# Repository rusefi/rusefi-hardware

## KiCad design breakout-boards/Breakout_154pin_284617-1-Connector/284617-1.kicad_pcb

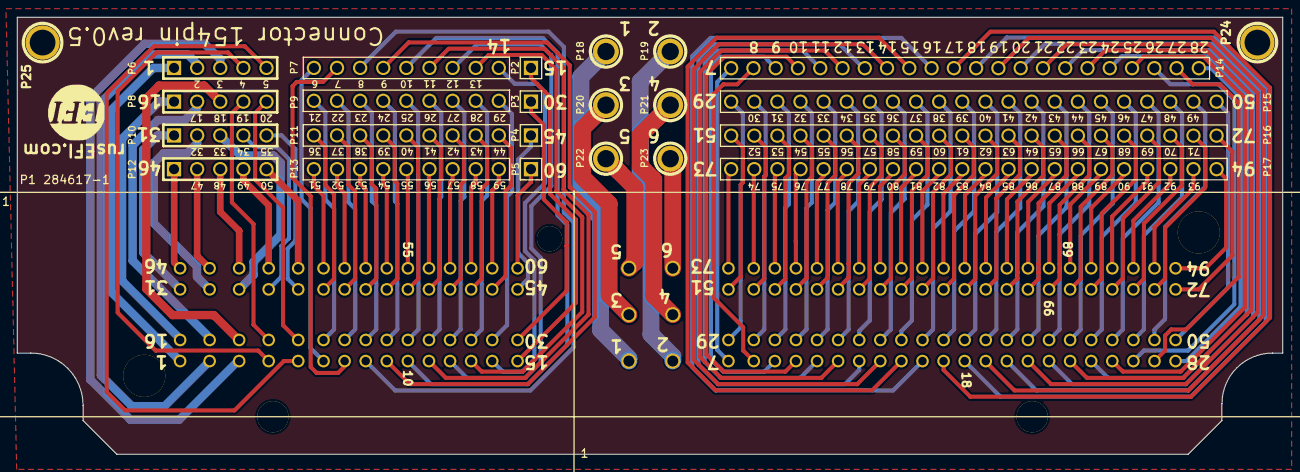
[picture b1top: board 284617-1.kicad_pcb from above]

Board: 2 copper layers, 150.0 x 51.8 mm, 27 parts (1 on the bottom side), 155 nets.

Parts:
G?: LOGO
G?#2: LOGO; LOGO_F
P1: 284617-1
P2, P3, P4, P5: CONN_1; PIN_ARRAY_1
P6, P8, P10, P12: CONN_5; PIN_ARRAY_5x1
P7, P9, P11, P13: CONN_9; PIN_ARRAY_9x1
P14, P15, P16, P17: CONN_22; PIN_ARRAY_22x1
P18, P19, P20, P21, P22, P23: CONN_1; 1pin(m)
P24, P25: CONN_1; 1pin

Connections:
/GND: P24.1, P25.1
unnamed: P1.94, P15.6
unnamed: P1.108, P15.20
unnamed: P1.107, P15.19
unnamed: P1.106, P15.18
unnamed: P1.105, P15.17
unnamed: P1.104, P15.16
unnamed: P1.103, P15.15
unnamed: P1.102, P15.14
unnamed: P1.101, P15.13
unnamed: P1.100, P15.12
unnamed: P1.99, P15.11
unnamed: P1.98, P15.10
unnamed: P1.97, P15.9
unnamed: P1.96, P15.8
unnamed: P1.95, P15.7
unnamed: P1.109, P15.21
unnamed: P1.93, P15.5
unnamed: P1.92, P15.4
unnamed: P1.91, P15.3
unnamed: P1.90, P15.2
unnamed: P1.89, P15.1
unnamed: P1.88, P14.22
unnamed: P1.87, P14.21
unnamed: P1.86, P14.20
unnamed: P1.85, P14.19
unnamed: P1.84, P14.18
unnamed: P1.83, P14.17
unnamed: P1.82, P14.16
unnamed: P1.81, P14.15
unnamed: P1.80, P14.14
unnamed: P1.123, P16.13
unnamed: P1.137, P17.5
unnamed: P1.136, P17.4
unnamed: P1.135, P17.3
unnamed: P1.134, P17.2
unnamed: P1.133, P17.1
unnamed: P1.132, P16.22
unnamed: P1.131, P16.21
unnamed: P1.130, P16.20
unnamed: P1.129, P16.19
unnamed: P1.128, P16.18
unnamed: P1.127, P16.17
unnamed: P1.126, P16.16
unnamed: P1.125, P16.15
unnamed: P1.124, P16.14
unnamed: P1.79, P14.13
unnamed: P1.122, P16.12
unnamed: P1.121, P16.11
unnamed: P1.120, P16.10
unnamed: P1.119, P16.9
unnamed: P1.118, P16.8
unnamed: P1.117, P16.7
unnamed: P1.116, P16.6
unnamed: P1.115, P16.5
unnamed: P1.114, P16.4
unnamed: P1.113, P16.3
unnamed: P1.112, P16.2
unnamed: P1.111, P16.1
unnamed: P1.110, P15.22
unnamed: P1.138, P17.6
unnamed: P1.78, P14.12
unnamed: P1.77, P14.11
unnamed: P1.76, P14.10
unnamed: P1.75, P14.9
unnamed: P1.74, P14.8
unnamed: P1.73, P14.7
unnamed: P1.72, P14.6
unnamed: P1.71, P14.5
unnamed: P1.70, P14.4
unnamed: P1.69, P14.3
unnamed: P1.68, P14.2
unnamed: P1.67, P14.1
unnamed: P1.154, P17.22
unnamed: P1.144, P17.12
unnamed: P1.153, P17.21
unnamed: P1.143, P17.11
unnamed: P1.152, P17.20
unnamed: P1.142, P17.10
unnamed: P1.151, P17.19
unnamed: P1.141, P17.9
unnamed: P1.150, P17.18
unnamed: P1.140, P17.8
unnamed: P1.147, P17.15
unnamed: P1.149, P17.17
unnamed: P1.139, P17.7
unnamed: P1.148, P17.16
unnamed: P1.146, P17.14
unnamed: P1.145, P17.13
unnamed: P1.62, P19.1
unnamed: P1.61, P18.1
unnamed: P1.45, P4.1
unnamed: P1.63, P20.1
unnamed: P1.66, P23.1
unnamed: P1.65, P22.1
unnamed: P1.64, P21.1
unnamed: P1.1, P6.1
unnamed: P1.59, P13.9
unnamed: P1.49, P12.4
unnamed: P1.60, P5.1
unnamed: P1.43, P11.8
unnamed: P1.33, P10.3
unnamed: P1.23, P9.3
unnamed: P1.13, P7.8
unnamed: P1.52, P13.2
unnamed: P1.42, P11.7
unnamed: P1.32, P10.2
unnamed: P1.22, P9.2
unnamed: P1.12, P7.7
unnamed: P1.51, P13.1
unnamed: P1.41, P11.6
unnamed: P1.31, P10.1
unnamed: P1.21, P9.1
unnamed: P1.11, P7.6
unnamed: P1.53, P13.3
unnamed: P1.50, P12.5
unnamed: P1.40, P11.5
unnamed: P1.30, P3.1
unnamed: P1.20, P8.5
unnamed: P1.10, P7.5
unnamed: P1.9, P7.4
unnamed: P1.8, P7.3
unnamed: P1.7, P7.2
unnamed: P1.6, P7.1
unnamed: P1.5, P6.5
unnamed: P1.4, P6.4
unnamed: P1.3, P6.3
unnamed: P1.2, P6.2
unnamed: P1.46, P12.1
unnamed: P1.39, P11.4
unnamed: P1.29, P9.9
unnamed: P1.19, P8.4
unnamed: P1.48, P12.3
unnamed: P1.38, P11.3
unnamed: P1.28, P9.8
unnamed: P1.18, P8.3
unnamed: P1.57, P13.7
unnamed: P1.47, P12.2
unnamed: P1.37, P11.2
unnamed: P1.27, P9.7
unnamed: P1.17, P8.2
unnamed: P1.56, P13.6
unnamed: P1.58, P13.8
unnamed: P1.36, P11.1
unnamed: P1.26, P9.6
unnamed: P1.16, P8.1
unnamed: P1.55, P13.5
unnamed: P1.35, P10.5
unnamed: P1.25, P9.5
unnamed: P1.15, P2.1
unnamed: P1.54, P13.4
unnamed: P1.44, P11.9
unnamed: P1.34, P10.4
unnamed: P1.24, P9.4
unnamed: P1.14, P7.9

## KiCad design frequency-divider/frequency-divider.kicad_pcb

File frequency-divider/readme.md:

We sometimes want to lower input frequency unless one does hard code periperal based magic.

https://github.com/rusefi/rusefi/issues/2935

https://github.com/rusefi/rusefi/issues/3412

https://github.com/rusefi/rusefi/issues/7133

See also https://github.com/rusefi/rusefi-hardware/tree/main/VR_ncv1124_test_module

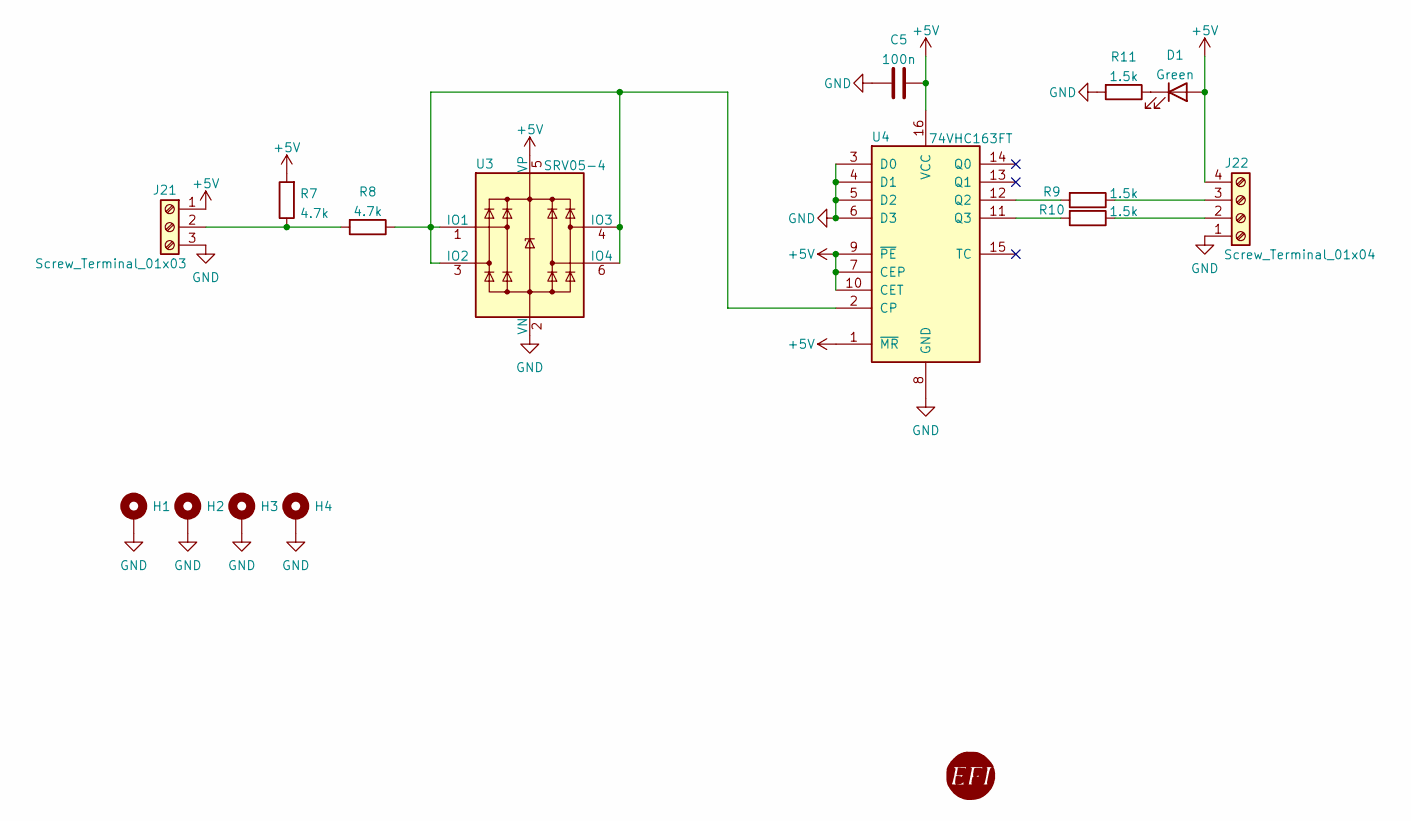
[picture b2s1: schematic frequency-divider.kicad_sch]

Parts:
C5: 100n; C_0603_1608Metric_Pad1.08x0.95mm_HandSolder; LCSC C14663
D1: Green; LED_0805_2012Metric_Pad1.15x1.40mm_HandSolder; LCSC C2297
G8: RUSEFI_LOGO; rusefi_logo
H1, H2, H3, H4: MountingHole_Pad; MountingHole_3.2mm_M3_Pad_Via
J21: Screw_Terminal_01x03; TerminalBlock_MetzConnect_Type055_RT01503HDWU_1x03_P5.00mm_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; LCSC C128026
J22: Screw_Terminal_01x04; TerminalBlock_MetzConnect_Type055_RT01504HDWU_1x04_P5.00mm_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; LCSC C173286
R7, R8: 4.7k; R_0603_1608Metric_Pad0.98x0.95mm_HandSolder; LCSC C23162
R9, R10, R11: 1.5k; R_0603_1608Metric_Pad0.98x0.95mm_HandSolder; LCSC C22843
U3: SRV05-4; SOT-23-6; LCSC C85364
U4: 74VHC163FT; TSSOP-16_4.4x5mm_P0.65mm; LCSC C150161

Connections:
+5V: C5.2, D1.2 (A), J21.1, J22.4, R7.2, U3.5 (VP), U4.1 (~MR), U4.7 (CEP), U4.9 (~PE), U4.10 (CET), U4.16 (VCC)
GND: C5.1, H1.1, H2.1, H3.1, H4.1, J21.3, J22.1, R11.2, U3.2 (VN), U4.3 (D0), U4.4 (D1), U4.5 (D2), U4.6 (D3), U4.8 (GND)
unnamed: D1.1 (K), R11.1
unnamed: J21.2, R7.1, R8.2
unnamed: J22.2, R10.1
unnamed: J22.3, R9.1
unnamed: R8.1, U3.1 (IO1), U3.3 (IO2), U3.4 (IO3), U3.6 (IO4), U4.2 (CP)
unnamed: R9.2, U4.12 (Q2)
unnamed: R10.2, U4.11 (Q3)

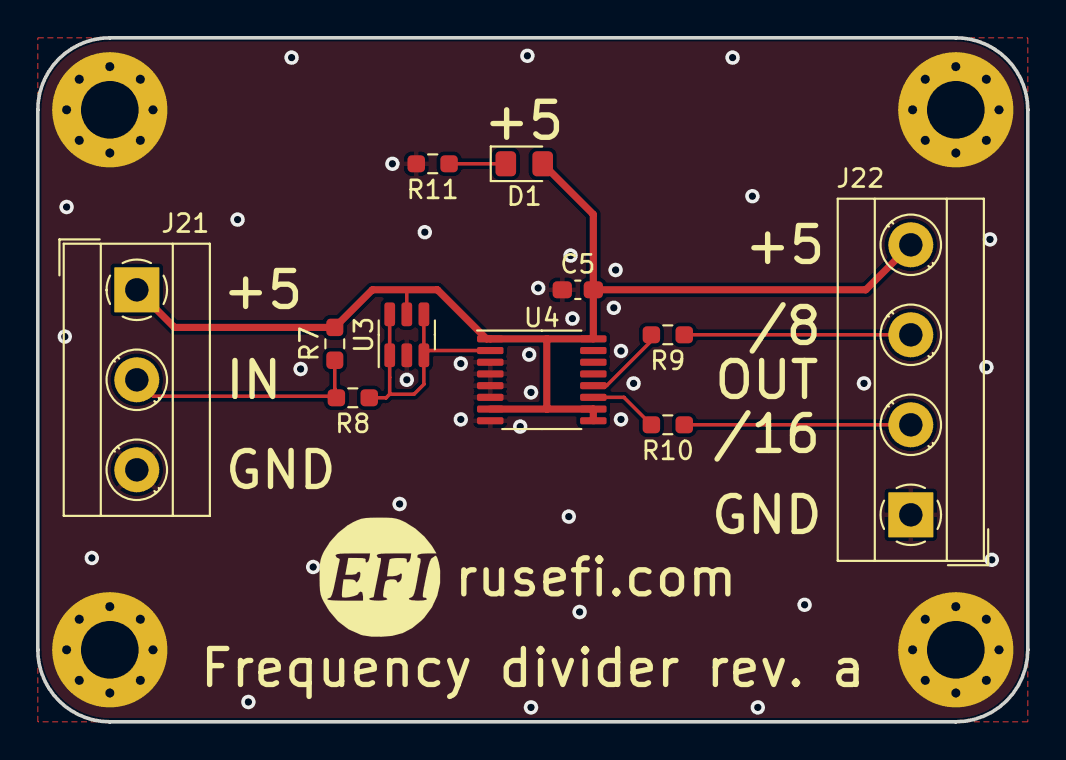
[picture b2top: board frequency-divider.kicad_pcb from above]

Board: 2 copper layers, 55.0 x 38.0 mm, 16 parts (0 on the bottom side), 9 nets.

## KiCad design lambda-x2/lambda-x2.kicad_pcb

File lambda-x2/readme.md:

# About

🟢 rev1 is known to work 🟢

pinout source https://github.com/rusefi/rusefi/tree/master/firmware/config/boards/lambda-x2

https://www.shop.rusefi.com/shop/p/dual-channel-wbo

Features:
* STM32F103 dual channel wideband AFR controller supporting Bosch LSU4.9 and LSU4.2 (LSU_ADV work in progress)
* CAN and analog output
* Bluetooth or USRT TunerStudio connectivity

Options (not icluded in default BOM)
* x2 EGT input using MAX31855KASA or MAX31856
* x2 auxilary analog input: 0..5V with pull-up or pull-down (configurable by soldering resistor). One can be used to source 5V to external sensor.
* x2 2 auxilary output 0..5V. Also can be used for slow PWM signal output.
* x2 open drain outputs

In development:
* MegaSquirt compatible pass-through connection over CAN http://www.msgpio.com/manuals/mshift/cpt.html (in progress)

See [interactive pinout](https://rusefi.com/docs/pinouts/lambda-x2/)

See [wire colors](https://github.com/rusefi/rusefi/wiki/WBO#naming-convention) for standart LSU wire collors and connectors pinouts.

Current stable [FW release](https://github.com/dron0gus/wideband/releases/tag/release_zero) use "dual-rev1" files

Firmware [sources](https://github.com/dron0gus/wideband) (based on https://github.com/mck1117/wideband).

See rusEFI forum: [F103 dual channel wideband controller + EGT + 2 x AUX In + 2 Aux out](https://rusefi.com/forum/viewtopic.php?f=4&t=2314)

See also https://github.com/rusefi/rusefi/wiki/WBO

# Known issues

## DFU mode/floating PB2

BOOT0 = 1, BOOT1 = 0 pattern is used to enter DFU bootloader on power/reset. BOOT0 is controled by jumper/button. BOOT1 (PB2) is used as bias current source for LSU4.9 and floating.

Use jumper wire to connect PB2 (through bias resistor) to GND: connect A2 pin of main connector with GND (J4 AUX connector pin 10)

## ESR measurement crosstalk between channels (rev0 and rev1)

HW has three different outputs for Nernst cell ESR measurement with different output resistance: 6.8K for LSU4.2, 22K for LSU4.9 and 47K for LSUADV. Idea was to allow the user to set the type of sensor from SW only.

Each ESR output is driven by one MCU GPIO. GPIOs for unused ESR measurement outputs are kept in Hi-Z (input) state and does not affect ESR measurement.

Same GPIO drivers ESR outputs for both channels. **This is the root cause of problem**

Problem: unused ESR output with GPIO in Hi-Z state connect Nernst cell outputs from left and right channel through two resistors. This causes crosstalk between channels and inaccurate ESR measurement. Wrong ESR measurement causes incorrect sensor temperature calculation. This can lead to inaccurate AFR measurement, overheating or underheating of the sensor.

Same issue for LSU4.9 bias resistors R22 and R70.

Solution:

Boards come with all ESR drive resistors populated. You have to remove unnecessary resistors.

If LSU4.2 sensor is used: remove R24, R25, R71, R72, R22, R70. Keep R41 and R73 - 6.8K

If LSU4.9 sensor is used: remove R25, R41, R72, R73. Keep R24 and R71 - 22K

If LSUADV sensor is used: remove R24, R41, R71, R73, R22, R70. Keep R25 and R72 - 47K

This will be (or not) solved in next revision of HW.

# Pinout

## Connectors pinout

[Main connector interactive Pinout](https://rusefi.com/docs/pinouts/lambda-x2/)

J4 is AUX connector available on PCB. SPI and I2C interfaces along with 3.3V and 5V are routed to this connector. Can be used to connect some small disply (SW not implemented yet)

J3 connector is for flashing and powering board on table. Also can be used for TunerStudion connection.

J1 and J2 are JTAG connectos.

## Uart pinout

J3 connector. Colors are default for cheap usb-to-uart converters based on CP2101 or FTDI232
Connect red wire if you want to power device from USB.
Default baud rate is 115200.

# Bluetooth

No extra steps needed to initialize JDY-33. Default device name is "RusEFI WBO x2" (or "RuseEFI WBO x2 BLE" for BT BLE)

Default baud rate is 115200.

# TunerStudio configuration

Baudrate is 115200
[.ini file](https://github.com/dron0gus/wideband/blob/master/firmware/ini/rusefi_wb_f1_dual.ini) for both UART and BT connection.

Both interfaces can be used simultaneously for data logging but not for settings change (from rev1).

Rev0 share same UART for both interfaces.

# Firmware Upload

Two ways to program using STM32CubeProgrammer

* recommended way: using UART connectivity. Power device up while shorting BOOT0 jumper to enter DFU mode (see "DFU mode/floating PB2" issue above)
* st-link if you have tc2030 spring-loaded cable.
* update over CAN or UART (J3) using OpenBLT (update over BT is in progress)

TL,DR: 9600 nothing connected on main connector

## Updating over UART using DFU mode

1. Disconnect main connector. If you are going to apply +12V power through main connector - make sure that nothing else is connected to WBO (LSU sensors, any load, etc). But I recommend flash using +5V from USB.
   
2. connect USB to uart connector to J3 connector: gnd, rx and tx.
Don't forget to cross Rx-`Tx (adapter's Tx goes to WBO's Rx, WBO's Tx goes to adapter's Rx).
If you going to power WBO from USB port - also attach 5V line. Do not connect +5 from USB adapter if you are going to use +12V supply through main connector.

### Linux way

3. Install stm32flash utility

`apt-get install stm32flash`

4. Press and hold BOOT0 button on the bottom of PCB. Or short BOOT0 PCB jumper if button is not populated on your board.

6. Run

`stm32flash /dev/ttyUSB0 -w wideband.hex`

### Windows way

3. Download and install STM32 Flash Loader Demonstrator. (Alternative tool is stm32flash - not covered in this instruction)

4. Figure out USB to serial serial port number: 

5. Start Flash Loader Demonstrator GUI application, select correct COM port. Optional: reduce timeout to 1 second:

6. Press and hold BOOT0 button on the bottom of PCB. Or short BOOT0 PCB jumper if button is not populated on your board.

7. Apply power (while holding BOOT0 button) to board and press Next in application. After app detects chip you should see something similar to:

8. Press next, select "Download to device", select wideband.bin file. Select "Jump to user application" and "Verify after download"

9. Press Next and wait for flash/verification ends.

## Updating using JTAG

DBD.

## Update using OpenBLT

OpenBLT https://www.feaser.com/openblt/doku.php

1. Restart device to OpenBLT mode using "Reset to OpenBLT" button under Controller -> ECU tools in TunerStudio.
   
2. Close TunerStudio to release serial port

3. Open BootCommander, select correct serial port, select wideband_update.srec file.

# Changelog

## rev 1
* Switch to 64 pin STM32/GD32
* Add 8MHz HSE oscillator (better clock stability for CAN over wide temperature range)
* Use DAC (instead of PWM) outputs for driving Ip
* Move BT to UART3/USART3, keep USART1 for bootloader/debug
* Drive BT's EN signal from MCU
* Fix RC filters on heater outputs for better voltage measurement
* Use separate ADC input for Vbat measurement
* Use ADC channels for AUX outputs monitoring/diagnostic
* Use PWM noise cancelation circuit on AUX analog outputs
* Removed useless/non-functional protection of Vm outputs
* Fix board outline to fit two types of enclosure ("plastic top" and "alloy brick")
* Add testpoints for TC2030 JTAG probe
* Add buttons for Reset and Boot0
* Add Cfg1 and jumpers
* Replace fuse holder with resettable 0.2A 33V fuse
* Two status LEDs for separate status indication for left and right channel
* Silkscreen labels around testpoints
* Silkscreen labels at uart connector on both sides of PCB
* Un_3x_sense formula is now 0.247 + 3.15 * (Un - Vm)
* Un_sense (not gained) is also routed to ADC input
* Protection from possible Ip current when MCU in reset/bootloader
* White "power on" LED replaced with green
* Main connector pinout added to top silkscreen
* AUX connector pinout added to top silkscreen

## rev 0

Seems to work with proper C10/C35 using https://github.com/rusefi/wideband/releases/tag/20230210-does-not-match-binaris

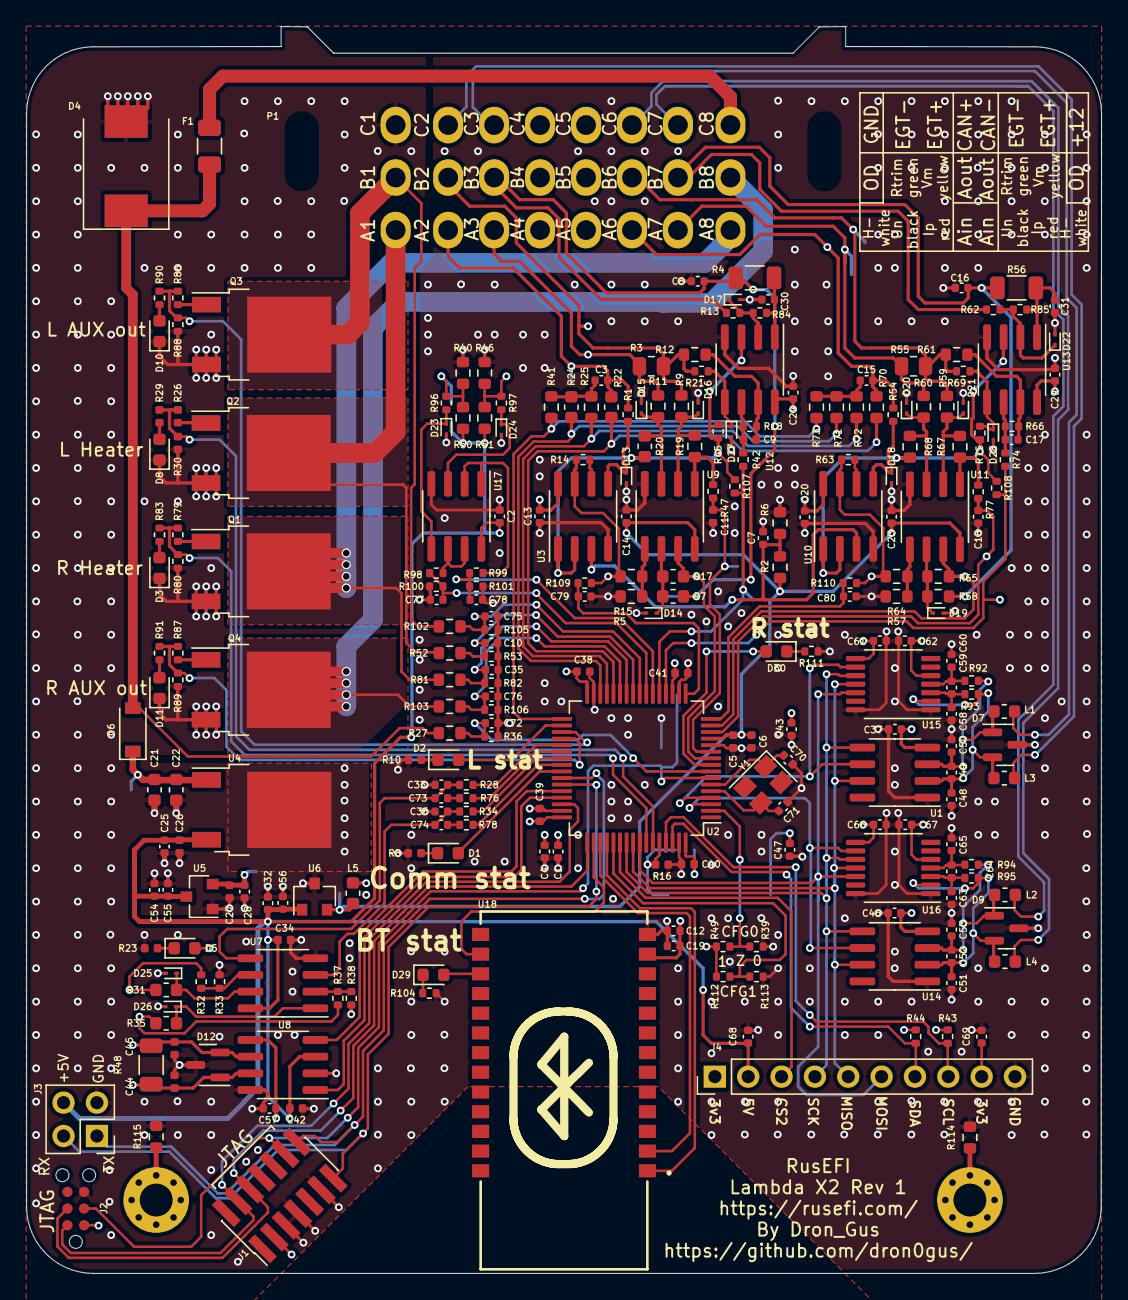
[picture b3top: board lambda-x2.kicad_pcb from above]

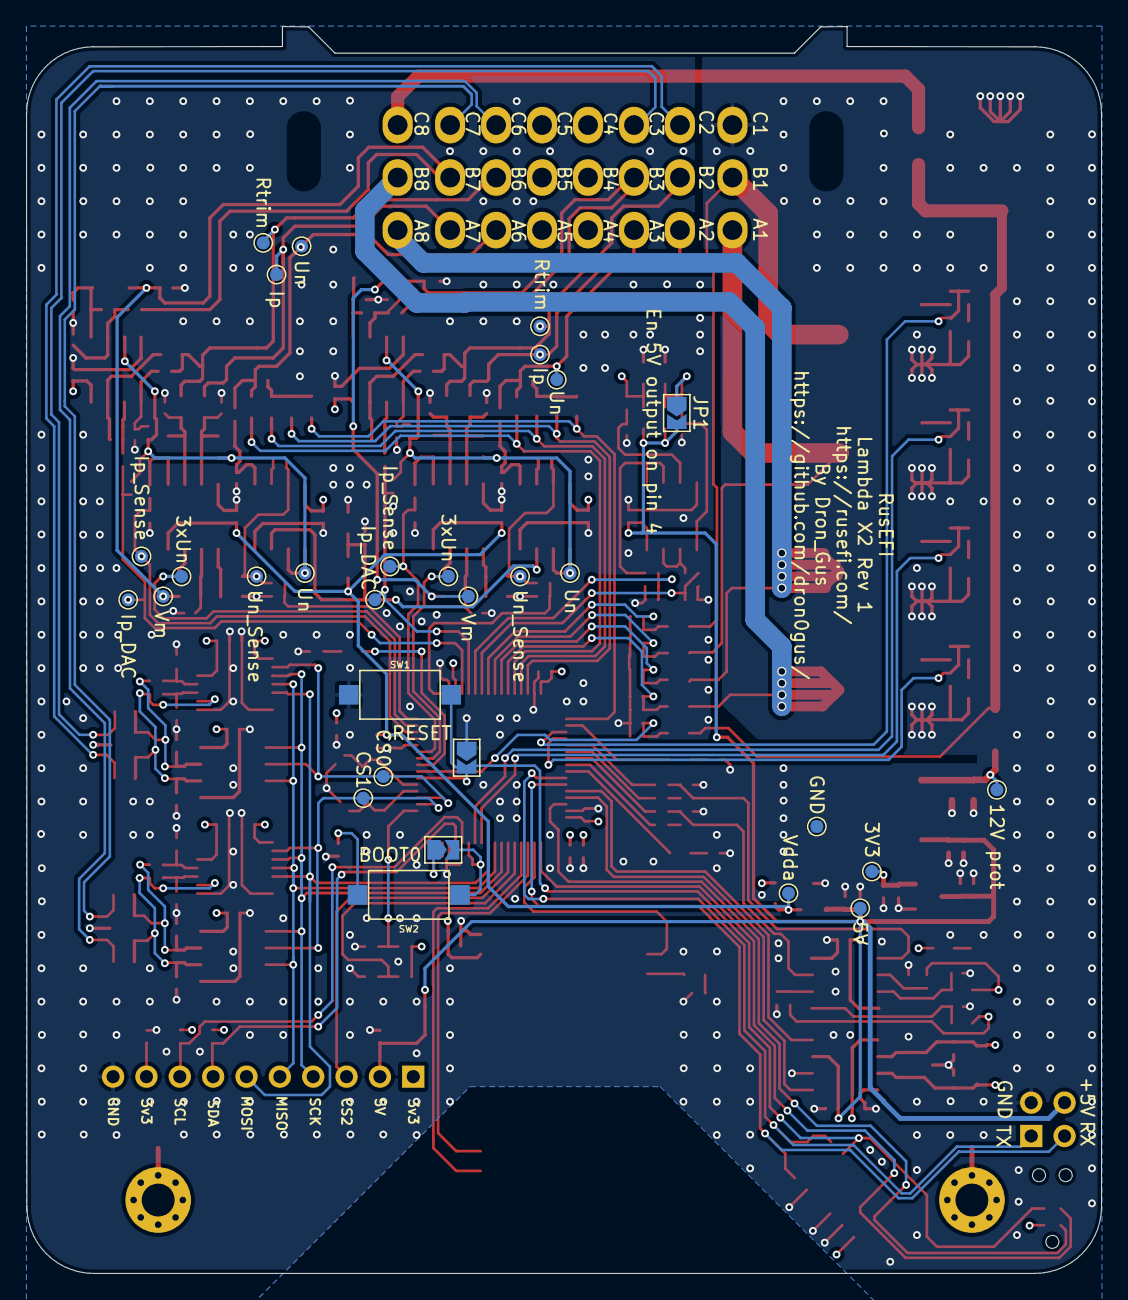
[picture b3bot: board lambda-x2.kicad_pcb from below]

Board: 4 copper layers, 81.9 x 95.0 mm, 291 parts (30 on the bottom side), 149 nets.

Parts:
C1, C6, C7, C8, C12, C16, C25, C28, C30, C31, C32, C43, C47, C54: 1u; C_0402_1005Metric
C2, C3, C5, C11, C13, C14, C15, C18, C19, C20, C23, C24, C26, C27, C29, C33, C34, C36, C37, C38, C39, C40, C41, C42, C46, C49, C52, C55, C56, C57, C59, C61, C62, C64, C66, C67, C68, C69, C73, C74: 100n; C_0402_1005Metric
C4: 4.7u; C_0402_1005Metric
C9, C17: 33n; C_0402_1005Metric
C10, C35, C72, C75, C76, C77, C78, C79, C80: 1n; C_0402_1005Metric
C21: 1u 25V; C_0603_1608Metric
C22: 100n 25V; C_0603_1608Metric
C44, C45: 47p; C_0402_1005Metric
C48, C50, C51, C53, C58, C60, C63, C65: 10nF 50V; C_0402_1005Metric
C70, C71: 20pF 50V; C_0402_1005Metric
D1: BLUE; LED_0603_1608Metric
D2, D5, D29, D30: GREEN; LED_0603_1608Metric
D3, D8, D10, D11: RED; LED_0603_1608Metric
D4: SMCJ22CA; D_SMC
D6: 1N4148W; D_SOD-123
D7, D9, D12: NUP2105L; SOT-23
D13, D14, D15, D16, D17, D18, D19, D20, D21, D22, D23, D24, D25, D26, D27, D28: ESD5V0D9B; D_SOD-923
F1: BSMD1206-025-33V; Fuse_1206_3216Metric
H1, H4: MountingHole_Pad; MountingHole_2.5mm_Pad_Via
J1: FTSH-107-01-F-DV-K; PinHeader_2x07_P1.27mm_Vertical_SMD
J2: tc2030-idc-nl
J3: Conn_02x02_Odd_Even; PinHeader_2x02_P2.54mm_Vertical
J4: Conn_01x10; PinHeader_1x10_P2.54mm_Vertical
JP1, JP2, JP3: SolderJumper_2_Open; SolderJumper-2_P1.3mm_Open_TrianglePad1.0x1.5mm
L1, L2, L3, L4, L5: 470R@100MHz; L_0603_1608Metric
P1: 33311-24AW-2
Q1, Q2, Q3, Q4: BTS3028; TO-252-2
R1, R14, R16, R18, R21, R30, R49, R54, R63, R66, R69, R80, R88, R89, R96, R97, R107, R108, R112: 10k; R_0402_1005Metric
R2, R5, R6, R7, R9, R11, R57, R58, R59, R60: 10k 0.1%; R_0603_1608Metric
R3, R55: 61.9R 1%; R_0805_2012Metric
R4, R56: 10R; R_1206_3216Metric
R8, R10, R23, R26, R29, R79, R83, R86, R87, R90, R91, R104, R109, R110, R111: 1k; R_0402_1005Metric
R12, R61, R114, R115: 47R; R_0603_1608Metric
R13, R36, R53, R62, R82, R84, R85, R105, R106: 10k 1%; R_0402_1005Metric
R15, R64: 2.7k 0.1%; R_0603_1608Metric
R17, R65: 30k 1%; R_0603_1608Metric
R19, R20, R67, R68: 100k 0.1%; R_0603_1608Metric
R22, R70: 62k 1%; R_0603_1608Metric
R24, R71: 22k 0.1%; R_0603_1608Metric
R25, R72: 47k 1%; R_0603_1608Metric
R27, R52, R81, R102, R103: 100k 1%; R_0603_1608Metric
R28, R34, R43, R44, R47, R76, R77, R78: 3.3k; R_0402_1005Metric
R31, R35: 330R; R_0603_1608Metric
R32, R37, R98, R99: 82k; R_0402_1005Metric
R33, R38, R100, R101: 160k; R_0402_1005Metric
R39, R113: 0R; R_0402_1005Metric
R40, R46, R50, R51: 1K; R_0603_1608Metric
R41, R73: 6.8k 0.1%; R_0603_1608Metric
R42, R45, R74, R75: 68k; R_0402_1005Metric
R48: 120R; R_1206_3216Metric
R92, R93, R94, R95: 100R; R_0402_1005Metric
SW1, SW2: SW_SPST_CK_RS282G05A3
TP3, TP4: Un_Sense; TestPoint_Pad_D1.0mm
TP5, TP6: 3xUn; TestPoint_Pad_D1.0mm
TP7: 5V; TestPoint_Pad_D1.0mm
TP8: 3V3; TestPoint_Pad_D1.0mm
TP9: Vdda; TestPoint_Pad_D1.0mm
TP10, TP17: Ip; TestPoint_Pad_D1.0mm
TP11, TP18: Rtrim; TestPoint_Pad_D1.0mm
TP12, TP19: Vm; TestPoint_Pad_D1.0mm
TP13, TP14, TP20, TP21: Un; TestPoint_Pad_D1.0mm
TP15, TP22: Ip_DAC; TestPoint_Pad_D1.0mm
TP16, TP23: Ip_Sense; TestPoint_Pad_D1.0mm
TP24: GND; TestPoint_Pad_D1.0mm
TP25: CS0; TestPoint_Pad_D1.0mm
TP26: CS1; TestPoint_Pad_D1.0mm
TP27: 12V prot; TestPoint_Pad_D1.0mm
U1, U14: MAX31855KASA; SOIC-8_3.9x4.9mm_P1.27mm
U2: STM32F103RCTx; LQFP-64_10x10mm_P0.5mm
U3, U7, U10, U12, U13, U17: MCP6002T-I/SN; SOIC-8_3.9x4.9mm_P1.27mm
U4: LM78M05_TO252; TO-252-2
U5: XC6206P332MR; SOT-23
U6: REF3033; SOT-23
U8: TJA1051T-3; SOIC-8_3.9x4.9mm_P1.27mm
U9, U11: GS8332-SR; SOIC-8_3.9x4.9mm_P1.27mm
U15, U16: MAX31856; TSSOP-14_4.4x5mm_P0.65mm
U18: JDY-33
Y1: XXDCELNANF-8MHZ; Crystal_SMD_3225-4Pin_3.2x2.5mm

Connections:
12V_RAW: F1.2, P1.24 (C8)
+3V3: C1.1, C4.1, C12.1, C13.1, C19.1, C20.1, C24.1, C27.1, C28.1, C29.1, C37.1, C38.1, C39.1, C40.1, C41.1, C43.1, C46.1, C47.1, C57.1, C61.1, C62.1, C66.1, C67.1, C69.1, D5.2 (A), J1.3, J2.1 (VCC), J4.1, J4.9, JP3.1 (A), L5.2, R43.1, R44.1, R49.2, R112.2, SW2.2, TP8.1, U1.4 (VCC), U2.19 (VDD), U2.32 (VDD), U2.48 (VDD), U2.64 (VDD), U3.8 (V+), U5.2 (VO), U8.5 (VIO), U10.8 (V+), U12.8 (V+), U13.8 (V+), U14.4 (VCC), U15.5 (AVDD), U15.8 (DVDD), U16.5 (AVDD), U16.8 (DVDD), U18.12 (3V3)
+5V: C2.1, C25.1, C26.1, C32.1, C34.1, C42.1, C54.1, C55.1, C56.1, C68.1, J3.4, J4.2, JP1.2 (B), R50.1, R51.1, TP7.1, U4.3 (VO), U5.3 (VI), U6.1 (IN), U7.8 (V+), U8.3 (VCC), U17.8 (V+)
/12V_sense: C72.1, R27.2, R36.2, U2.8 (PC0)
/BT_EN: U2.50 (PA15), U18.15 (EN)
/BT_UART_RX: U2.52 (PC11), U18.1 (TXD)
/BT_UART_TX: U2.51 (PC10), U18.2 (RXD)
/Boot0: JP3.2 (B), R16.2, SW2.1, U2.60 (BOOT0)
/CAN_H: C44.2, D12.1 (K), P1.20 (C4), R48.1, U8.7 (CANH)
/CAN_L: C45.1, D12.2 (K), P1.21 (C5), R48.2, U8.6 (CANL)
/CAN_RX: U2.44 (PA11), U8.4 (RXD)
/CAN_TX: U2.45 (PA12), U8.1 (TXD)
/DACout1: C33.1, C73.2, R28.2, U7.5 (+)
/DACout2: C36.1, C74.2, R34.2, U7.3 (+)
/I2C1_SCL: J4.8, R43.2, U2.61 (PB8)
/I2C1_SDA: J4.7, R44.2, U2.62 (PB9)
/LED_BLUE: D1.2 (A), U2.41 (PA8)
/LSU analog left/Un_sense: R14.2, R15.2, R109.1, TP3.1, U3.7
/LSU analog left/Vgnd_ref: C7.1, R2.2, R6.1, U3.3 (+), U10.3 (+)
/LSU analog right/Un_sense: R63.2, R64.2, R110.1, TP4.1, U10.7
/L_AUX: JP1.1 (A), P1.4 (A4), R40.1, R50.2, R96.1
/L_AUX_ADC: C77.1, R98.1, R100.2, U2.23 (PA7)
/L_EGT+: L1.1, P1.19 (C3)
/L_EGT-: L3.1, P1.18 (C2)
/L_Heater_sense: C10.1, R52.2, R53.2, U2.25 (PC5)
/L_Ip_dac: R42.1, R107.1, TP15.1, U2.21 (PA5)
/L_Ip_sense: C11.1, R47.1, TP16.1, U2.11 (PC3)
/L_LED_GREEN: D2.2 (A), U2.34 (PB13)
/L_LSU_Heater-: P1.1 (A1), Q2.2 (D), R52.1
/L_LSU_Ip: P1.3 (A3), R3.2, R11.2, TP10.1
/L_LSU_Rtrim: P1.10 (B2), R3.1, R9.2, R12.1, R21.1, TP11.1
/L_LSU_Un: C3.1, P1.2 (A2), R1.1, R22.2, TP13.1
/L_LSU_Vm: C8.1, P1.11 (B3), R4.1, R7.2, R13.1, TP12.1
/L_OD: P1.9 (B1), Q3.2 (D), R102.1
/L_OUT_en: R86.2, R88.2, R90.2, U2.35 (PB14)
/L_OUT_sense: C75.1, R102.2, R105.2, U2.24 (PC4)
/L_Un_3x_sense: R17.2, TP5.1, U2.10 (PC2), U9.7
/L_Un_sense: C79.1, R109.2, U2.17 (PA3)
/L_heater_pwm: R26.2, R29.2, R30.2, U2.59 (PB7)
/Nernst_4.2_esr_drive: R41.2, R73.2, U2.33 (PB12)
/Nernst_4.9_bias: R22.1, R70.1, U2.28 (PB2)
/Nernst_4.9_esr_drive: R24.2, R71.2, U2.30 (PB11)
/Nernst_ADV_esr_drive: R25.2, R72.2, U2.29 (PB10)
/R_AUX: P1.5 (A5), R46.1, R51.2, R97.1
/R_AUX_ADC: C78.1, R99.1, R101.2, U2.22 (PA6)
/R_EGT+: L2.1, P1.23 (C7)
/R_EGT-: L4.1, P1.22 (C6)
/R_Heater_sense: C35.1, R81.2, R82.2, U2.26 (PB0)
/R_Ip_dac: R74.1, R108.1, TP22.1, U2.20 (PA4)
/R_Ip_sense: C18.1, R77.1, TP23.1, U2.14 (PA0)
/R_LED_GREEN: D30.2 (A), U2.9 (PC1)
/R_LSU_Heater-: P1.8 (A8), Q1.2 (D), R81.1
/R_LSU_Ip: P1.7 (A7), R55.2, R60.2, TP17.1
/R_LSU_Rtrim: P1.14 (B6), R55.1, R59.2, R61.1, R69.1, TP18.1
/R_LSU_Un: C15.1, P1.6 (A6), R54.1, R70.2, TP20.1
/R_LSU_Vm: C16.1, P1.15 (B7), R56.1, R58.2, R62.1, TP19.1
/R_OD: P1.16 (B8), Q4.2 (D), R103.1
/R_OUT_en: R87.2, R89.2, R91.2, U2.36 (PB15)
/R_OUT_sense: C76.1, R103.2, R106.2, U2.27 (PB1)
/R_Un_3x_sense: R65.2, TP6.1, U2.15 (PA1), U11.7
/R_Un_sense: C80.1, R110.2, U2.16 (PA2)
/R_heater_pwm: R79.2, R80.2, R83.2, U2.58 (PB6)
/SPI1_CS0: TP25.1, U1.6 (~CS), U2.4 (PC15), U15.9 (~CS)
/SPI1_CS1: TP26.1, U2.3 (PC14), U14.6 (~CS), U16.9 (~CS)
/SPI1_CS2: J4.3, U2.54 (PD2)
/SPI1_MISO: J4.5, U1.7 (SO), U2.56 (PB4), U14.7 (SO), U15.11 (SDO), U16.11 (SDO)
/SPI1_MOSI: J4.6, U2.57 (PB5), U15.12 (SDI), U16.12 (SDI)
/SPI1_SCK: J4.4, U1.5 (SCK), U2.55 (PB3), U14.5 (SCK), U15.10 (SCK), U16.10 (SCK)
/SWCLK: J1.6, J2.4 (SWCLK), U2.49 (PA14)
/SWDIO: J1.4, J2.2 (SWDIO), U2.46 (PA13)
/UART_RX: J1.13, J3.2, U2.43 (PA10)
/UART_TX: J1.14, J3.1, U2.42 (PA9)
/Vout1: P1.13 (B5), R31.2, R32.2
/Vout2: P1.12 (B4), R35.2, R37.2
/config0: R39.1, R49.1, U2.2 (PC13)
/config1: R112.1, R113.1, U2.53 (PC12)
/nRESET: J1.12, J2.3 (NRESET), JP2.2 (B), SW1.2, U2.7 (NRST)
GND: C1.2, C2.2, C4.2, C5.2, C6.2, C7.2, C8.2, C10.2, C11.2, C12.2, C13.2, C14.2, C16.2, C18.2, C19.2, C20.2, C21.2, C22.2, C23.2, C24.2, C25.2, C26.2, C27.2, C28.2, C29.2, C30.2, C31.2, C32.2, C33.2, C34.2, C35.2, C36.2, C37.2, C38.2, C39.2, C40.2, C41.2, C42.2, C43.2, C44.1, C45.2, C46.2, C47.2, C48.2, C50.2, C51.2, C53.2, C54.2, C55.2, C56.2, C57.2, C58.2, C60.2, C61.2, C62.2, C63.2, C65.2, C66.2, C67.2, C68.2, C69.2, C70.1, C71.1, C72.2, C75.2, C76.2, C77.2, C78.2, C79.2, C80.2, D3.1 (K), D4.2 (A2), D7.3 (A), D8.1 (K), D9.3 (A), D10.1 (K), D11.1 (K), D12.3 (A), D13.2 (A2), D14.2 (A2), D15.2 (A2), D16.2 (A2), D17.2 (A2), D18.2 (A2), D19.2 (A2), D20.2 (A2), D21.2 (A2), D22.2 (A2), D23.2 (A2), D24.2 (A2), D25.2 (A2), D26.2 (A2), D27.2 (A2), D28.2 (A2), J1.5, J1.7, J1.11, J2.5 (GND), J3.3, J4.10, JP2.1 (A), P1.17 (C1), Q1.3 (S), Q2.3 (S), Q3.3 (S), Q4.3 (S), R5.1, R6.2, R8.1, R10.1, R16.1, R23.1, R30.1, R33.1, R36.1, R38.1, R39.2, R40.2, R46.2, R53.1, R57.1, R80.1, R82.1, R88.1, R89.1, R100.1, R101.1, R104.1, R105.1, R106.1, R111.1, R113.2, R114.2, R115.2, SW1.1, TP24.1, U1.1 (GND), U2.12 (VSSA), U2.18 (VSS), U2.31 (VSS), U2.47 (VSS), U2.63 (VSS), U3.4 (V-), U4.2 (GND), U5.1 (GND), U6.3 (GND), U7.4 (V-), U8.2 (GND), U8.8 (S), U9.4 (V-), U10.4 (V-), U11.4 (V-), U12.4 (V-), U13.4 (V-), U14.1 (GND), U15.1 (AGND), U15.14 (DGND), U16.1 (AGND), U16.14 (DGND), U17.4 (V-), U18.13 (GND)
unnamed: C3.2, R24.1, R25.1, R41.1
unnamed: C9.1, R12.2, R18.1, U12.7
unnamed: C9.2, R18.2, R42.2, U12.6 (-)
unnamed: C15.2, R71.1, R72.1, R73.1
unnamed: C17.1, R61.2, R66.1, U13.7
unnamed: C17.2, R66.2, R74.2, U13.6 (-)
unnamed: C21.1, C22.1, D6.1 (K), TP27.1, U4.1 (VI)
unnamed: C30.1, R4.2, R84.1, U12.1
unnamed: C31.1, R56.2, R85.1, U13.1
unnamed: C48.1, C49.1, D7.2 (K), L3.2, R93.1, U1.2 (T-), U15.2 (BIAS)
unnamed: C49.2, C50.1, D7.1 (K), L1.2, R92.1, U1.3 (T+)
unnamed: C51.1, C52.1, D9.2 (K), L4.2, R95.1, U14.2 (T-), U16.2 (BIAS)
unnamed: C52.2, C53.1, D9.1 (K), L2.2, R94.1, U14.3 (T+)
unnamed: C58.1, C59.1, R93.2, U15.3 (T-)
unnamed: C59.2, C60.1, R92.2, U15.4 (T+)
unnamed: C63.1, C64.1, R95.2, U16.3 (T-)
unnamed: C64.2, C65.1, R94.2, U16.4 (T+)
unnamed: C70.2, U2.6 (PD1), Y1.1
unnamed: C71.2, U2.5 (PD0), Y1.3
unnamed: C73.1, R76.2
unnamed: C74.1, R78.2
unnamed: D1.1 (K), R8.2
unnamed: D2.1 (K), R10.2
unnamed: D3.2 (A), R83.1
unnamed: D4.1 (A1), D6.2 (A), F1.1, R27.1
unnamed: D5.1 (K), R23.2
unnamed: D8.2 (A), R29.1
unnamed: D10.2 (A), R90.1
unnamed: D11.2 (A), R91.1
unnamed: D13.1 (A1), R1.2, U3.5 (+)
unnamed: D14.1 (A1), R7.1, R17.1, U9.6 (-)
unnamed: D15.1 (A1), R11.1, R20.1, U9.3 (+)
unnamed: D16.1 (A1), R9.1, R19.2, U9.2 (-)
unnamed: D17.1 (A1), R13.2, R84.2, U12.2 (-)
unnamed: D18.1 (A1), R54.2, U10.5 (+)
unnamed: D19.1 (A1), R58.1, R65.1, U11.6 (-)
unnamed: D20.1 (A1), R60.1, R68.1, U11.3 (+)
unnamed: D21.1 (A1), R59.1, R67.2, U11.2 (-)
unnamed: D22.1 (A1), R62.2, R85.2, U13.2 (-)
unnamed: D23.1 (A1), R96.2, U17.5 (+)
unnamed: D24.1 (A1), R97.2, U17.3 (+)
unnamed: D25.1 (A1), R31.1, U7.7
unnamed: D26.1 (A1), R35.1, U7.1
unnamed: D27.1 (A1), R21.2, R45.1, U12.5 (+)
unnamed: D28.1 (A1), R69.2, R75.1, U13.5 (+)
unnamed: D29.1 (K), R104.2
unnamed: D29.2 (A), U18.16 (ALED)
unnamed: D30.1 (K), R111.2
unnamed: H1.1, R114.1
unnamed: H4.1, R115.1
unnamed: Q1.1 (G), R79.1
unnamed: Q2.1 (G), R26.1
unnamed: Q3.1 (G), R86.1
unnamed: Q4.1 (G), R87.1
unnamed: R14.1, U3.6 (-)
unnamed: R5.2, R15.1, U9.5 (+)
unnamed: R19.1, R47.2, U9.1
unnamed: R28.1, U2.37 (PC6)
unnamed: R32.1, R33.2, U7.6 (-)
unnamed: R34.1, U2.39 (PC8)
unnamed: R37.1, R38.2, U7.2 (-)
unnamed: R57.2, R64.1, U11.5 (+)
unnamed: R63.1, U10.6 (-)
unnamed: R67.1, R77.2, U11.1
unnamed: R76.1, U2.38 (PC7)
unnamed: R78.1, U2.40 (PC9)
unnamed: R98.2, U17.6 (-), U17.7
unnamed: R99.2, U17.1, U17.2 (-)
unnamed: R20.2, R45.2, R107.2, TP14.1, U3.1, U3.2 (-), U12.3 (+)
unnamed: R68.2, R75.2, R108.2, TP21.1, U10.1, U10.2 (-), U13.3 (+)
VDDA: C5.1, C6.1, C14.1, C23.1, L5.1, R2.1, TP9.1, U2.13 (VDDA), U6.2 (OUT), U9.8 (V+), U11.8 (V+)

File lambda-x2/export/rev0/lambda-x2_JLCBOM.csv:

Comment,Designator,Footprint,LCSC
"1u","C1,C6,C7,C8,C12,C16,C25,C28,C32,C43,C47,C54","Capacitor_SMD:C_0402_1005Metric","C52923"
"100n","C2,C3,C5,C11,C13,C14,C15,C18,C19,C20,C23,C24,C26,C27,C29,C34,C37,C38,C39,C40,C41,C42,C46,C49,C52,C55,C56,C57,C59,C61,C62,C64,C66,C67,C68,C69","Capacitor_SMD:C_0402_1005Metric","C1525"
"10n","C10,C35","Capacitor_SMD:C_0402_1005Metric","C15195"
"1u  25V","C21","Capacitor_SMD:C_0603_1608Metric","C15849"
"100n  25V","C22","Capacitor_SMD:C_0603_1608Metric","C14663"
"2.2u","C33,C36","Capacitor_SMD:C_0402_1005Metric","C12530"
"4.7u","C4","Capacitor_SMD:C_0402_1005Metric","C23733"
"47p","C44,C45","Capacitor_SMD:C_0402_1005Metric","C1567"
"33n","C9,C17","Capacitor_SMD:C_0402_1005Metric","C1585"
"BLUE","D1","LED_SMD:LED_0603_1608Metric","C72041"
"NUP2105L","D7,D9,D12","Package_TO_SOT_SMD:SOT-23","C284104"
"GREEN","D2,D29","LED_SMD:LED_0603_1608Metric","C72043"
"ESD5V0D9B","D13,D14,D15,D16,D17,D18,D19,D20,D21,D22,D23,D24,D25,D26,D27,D28","Diode_SMD:D_SOD-923","C484329"
"RED","D3,D8,D10,D11","LED_SMD:LED_0603_1608Metric","C2286"
"SMCJ22CA","D4","Diode_SMD:D_SMC","C310038"
"WHITE","D5","LED_SMD:LED_0603_1608Metric","C2290"
"1N4148W","D6","Diode_SMD:D_SOD-123","C81598"
"XF-506P","F1","wideband_controller:XF-506P","C492610"
"470R@100MHz","L1,L2,L3,L4","Inductor_SMD:L_0603_1608Metric","C97853"
"33311-24AW-2","P1","local:33311-24AW-2",""
"BTS3028","Q1,Q2,Q3,Q4","Package_TO_SOT_SMD:TO-252-2","C112639"
"47R","R12,R61","Resistor_SMD:R_0603_1608Metric","C328363"
"10k","R1,R14,R16,R18,R21,R27,R30,R36,R49,R54,R63,R66,R69,R80,R88,R89","Resistor_SMD:R_0402_1005Metric","C25744"
"100k 0.1%","R19,R20,R67,R68","Resistor_SMD:R_0603_1608Metric","C122538"
"10k 0.1%","R2,R6,R7,R9,R11,R15,R58,R59,R60,R64,R96,R97","Resistor_SMD:R_0603_1608Metric","C309083"
"62k 1%","R22,R70","Resistor_SMD:R_0603_1608Metric","C23221"
"22k 0.1%","R24,R71","Resistor_SMD:R_0603_1608Metric","C133163"
"47k 1%","R25,R72","Resistor_SMD:R_0603_1608Metric","C25819"
"3.3k","R28,R34,R43,R44,R47,R77","Resistor_SMD:R_0402_1005Metric","C25890"
"61.9R 1%","R3,R55","Resistor_SMD:R_0805_2012Metric","C322537"
"330R","R31,R35","Resistor_SMD:R_0603_1608Metric","C23138"
"82k","R32,R37,R98,R99","Resistor_SMD:R_0603_1608Metric","C23254"
"160k","R33,R38,R100,R101","Resistor_SMD:R_0603_1608Metric","C22813"
"10R","R4,R56","Resistor_SMD:R_1206_3216Metric","C17903"
"6.8k 0.1%","R41,R73","Resistor_SMD:R_0603_1608Metric","C705876"
"68k","R42,R45,R74,R75","Resistor_SMD:R_0402_1005Metric","C36871"
"30k 1%","R5,R17,R57,R65","Resistor_SMD:R_0603_1608Metric","C22984"
"1K","R50,R51","Resistor_SMD:R_0603_1608Metric","C21190"
"100k 1%","R52,R81","Resistor_SMD:R_0402_1005Metric","C25741"
"10k 1%","R13,R53,R62,R82","Resistor_SMD:R_0402_1005Metric","C25744"
"1k","R8,R10,R23,R26,R29,R79,R83,R86,R87,R90,R91,R104","Resistor_SMD:R_0402_1005Metric","C11702"
"100R","R92,R93,R94,R95","Resistor_SMD:R_0402_1005Metric","C106233"
"MAX31855KASA","U1,U14","Package_SO:SOIC-8_3.9x4.9mm_P1.27mm",""
"STM32F103C6Tx","U2","Package_QFP:LQFP-48_7x7mm_P0.5mm",""
"LM78M05_TO252","U4","Package_TO_SOT_SMD:TO-252-2","C58069"
"XC6206P332MR","U5","Package_TO_SOT_SMD:SOT-23","C5446"
"REF3033","U6","Package_TO_SOT_SMD:SOT-23","C36658"
"MCP6002T-I/SN","U3,U7,U10,U12,U13,U17","Package_SO:SOIC-8_3.9x4.9mm_P1.27mm","C7377"
"TJA1051T-3","U8","Package_SO:SOIC-8_3.9x4.9mm_P1.27mm","C38695"
"GS8332-SR","U9,U11","Package_SO:SOIC-8_3.9x4.9mm_P1.27mm","C157713"
